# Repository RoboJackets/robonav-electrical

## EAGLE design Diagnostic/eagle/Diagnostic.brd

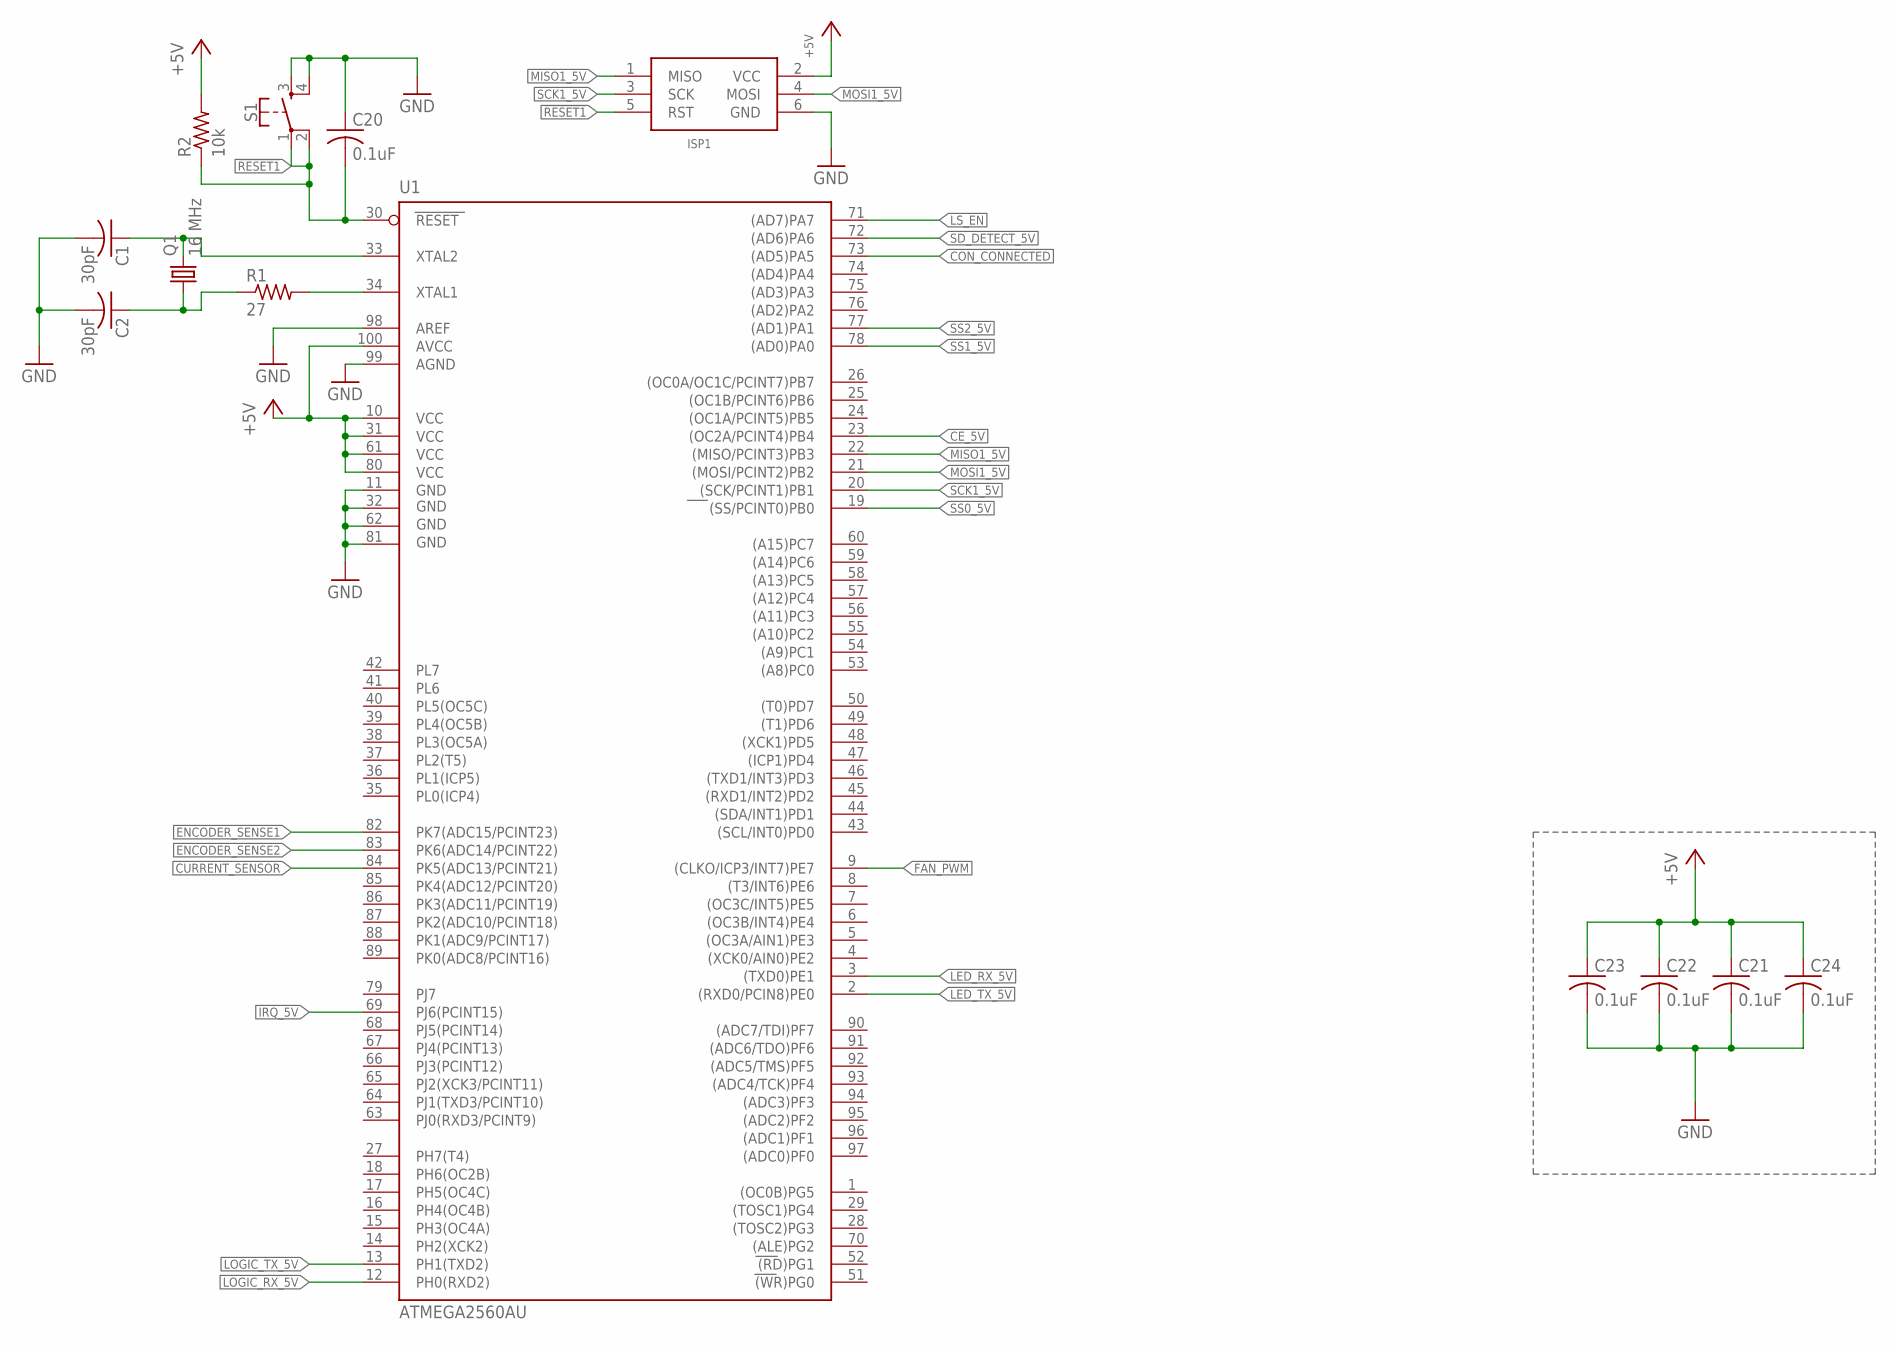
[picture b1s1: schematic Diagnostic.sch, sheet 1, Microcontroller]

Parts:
C1, C2: 30pF; C0603
C20, C21, C22, C23, C24: 0.1uF; C0603
ISP1: AVRISP-6; AVRISP
Q1: 16 MHz; HC49UP
R1: 27; R0603
R2: 10k; R0603
S1: MOMENTARY-SWITCH-SPST-2-SMD-5.2MM; TACTILE_SWITCH_SMD_5.2MM
U1: ATMEGA2560AU; TQFP100

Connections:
!RESET1: C20.2, ISP1.5 (RST), R2.1, S1.1, S1.2, U1.30 (RESET)
CE_5V: U1.23 ((OC2A/PCINT4)PB4); also elsewhere on the board
CON_CONNECTED: U1.73 ((AD5)PA5); also elsewhere on the board
CURRENT_SENSOR: U1.84 (PK5(ADC13/PCINT21)); also elsewhere on the board
ENCODER_SENSE1: U1.82 (PK7(ADC15/PCINT23)); also elsewhere on the board
ENCODER_SENSE2: U1.83 (PK6(ADC14/PCINT22)); also elsewhere on the board
FAN_PWM: U1.9 ((CLKO/ICP3/INT7)PE7); also elsewhere on the board
GND: C1.2, C2.2, C20.1, C21.2, C22.2, C23.2, C24.2, ISP1.6 (GND), S1.3, S1.4, U1.11 (GND), U1.32 (GND1), U1.62 (GND2), U1.81 (GND3), U1.98 (AREF), U1.99 (AGND); also elsewhere on the board
IRQ_5V: U1.69 (PJ6(PCINT15)); also elsewhere on the board
LED_RX_5V: U1.3 ((TXD0)PE1); also elsewhere on the board
LED_TX_5V: U1.2 ((RXD0/PCIN8)PE0); also elsewhere on the board
LOGIC_RX_5V: U1.12 (PH0(RXD2)); also elsewhere on the board
LOGIC_TX_5V: U1.13 (PH1(TXD2)); also elsewhere on the board
LS_EN: U1.71 ((AD7)PA7); also elsewhere on the board
MISO1_5V: ISP1.1 (MISO), U1.22 ((MISO/PCINT3)PB3); also elsewhere on the board
MOSI1_5V: ISP1.4 (MOSI), U1.21 ((MOSI/PCINT2)PB2); also elsewhere on the board
unnamed: C2.1, Q1.1, R1.1
unnamed: C1.1, Q1.2, U1.33 (XTAL2)
unnamed: R1.2, U1.34 (XTAL1)
SCK1_5V: ISP1.3 (SCK), U1.20 ((SCK/PCINT1)PB1); also elsewhere on the board
SD_DETECT_5V: U1.72 ((AD6)PA6); also elsewhere on the board
SS0_5V: U1.19 ((SS/PCINT0)PB0); also elsewhere on the board
SS1_5V: U1.78 ((AD0)PA0); also elsewhere on the board
SS2_5V: U1.77 ((AD1)PA1); also elsewhere on the board

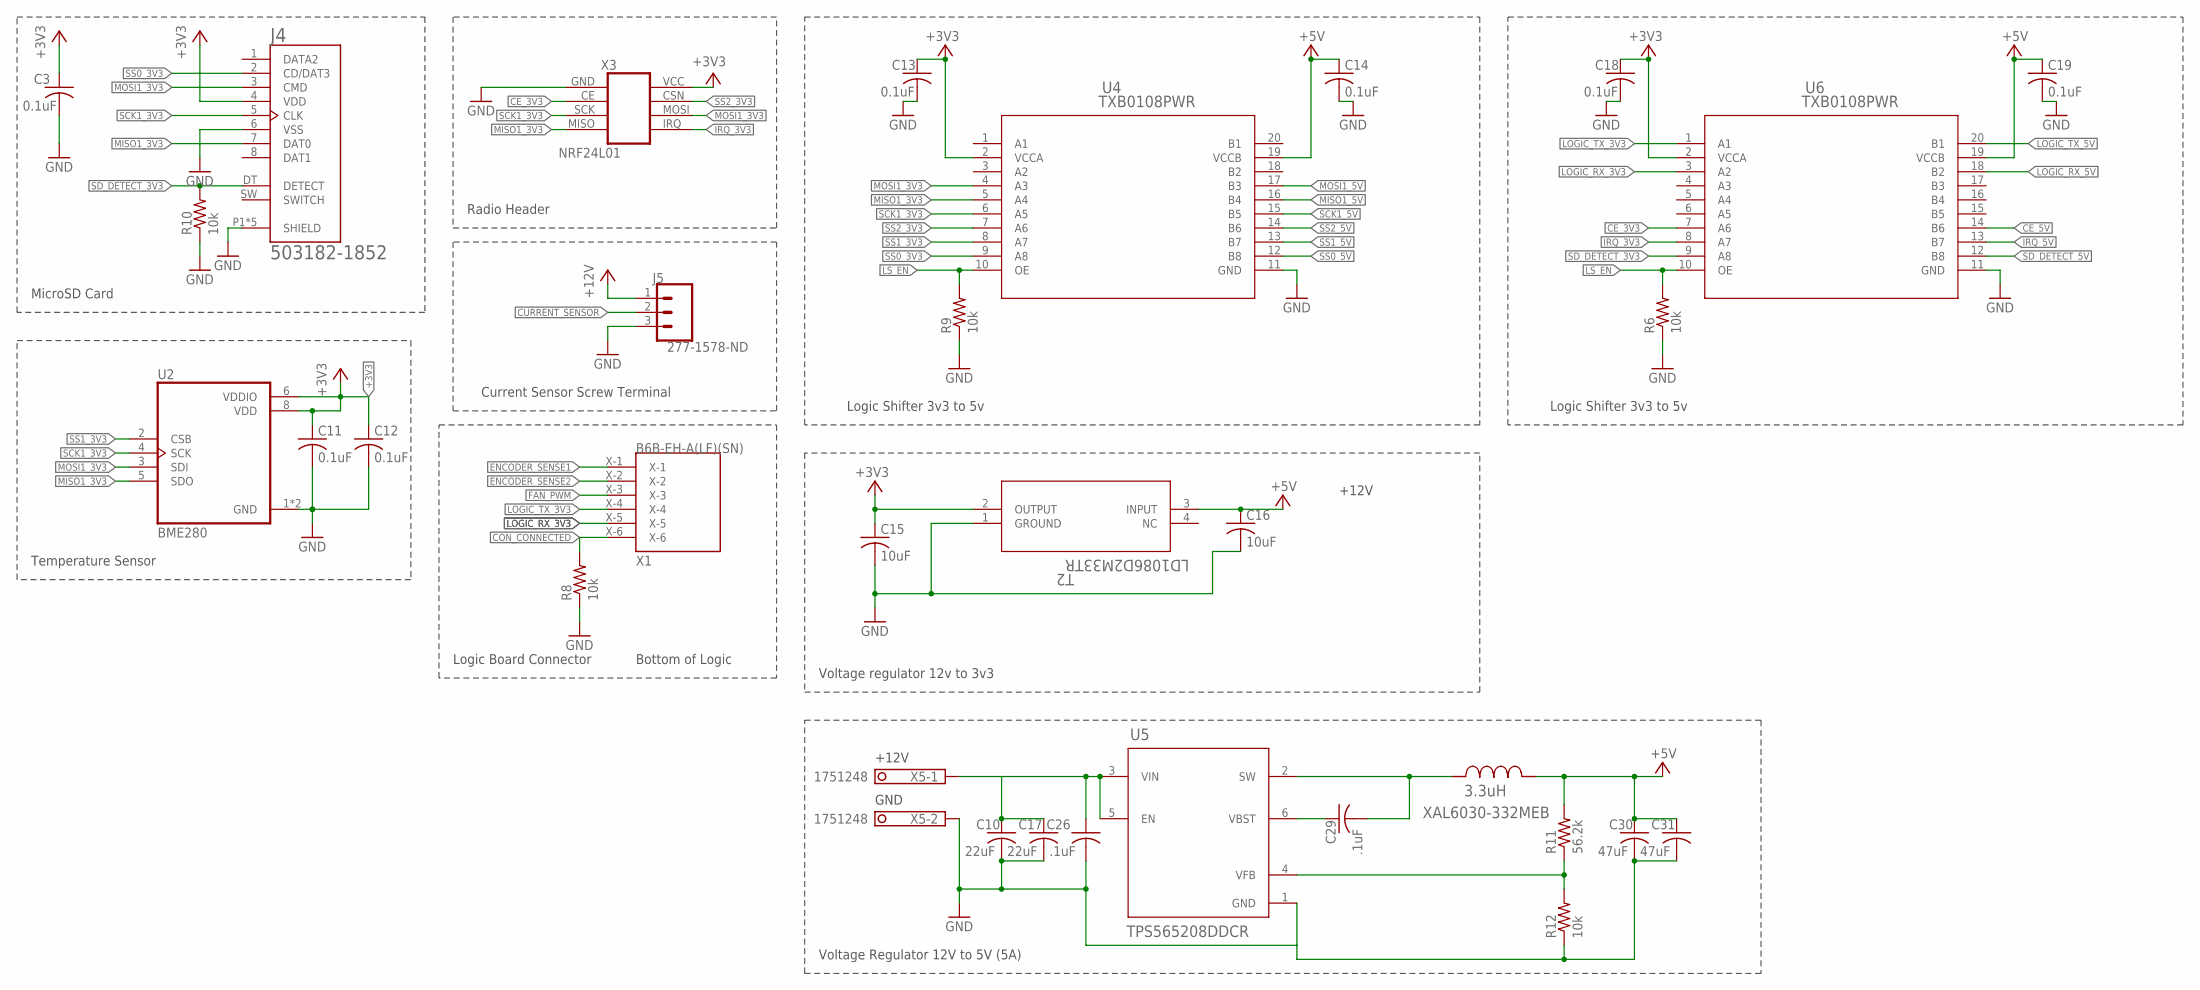
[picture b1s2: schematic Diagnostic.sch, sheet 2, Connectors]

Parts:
C3, C11, C12, C13, C14, C18, C19: 0.1uF; C0603
C10, C17: 22uF; C0603
C15, C16: 10uF; C1206
C26, C29: .1uF; C0603
C30, C31: 47uF; C0603
J4: 503182-1852; MOLEX_503182-1852
J5: 277-1578-ND; SCREWTERMINAL-5MM-3
R6, R8, R9, R10, R12: 10k; R0603
R11: 56.2k; R0603
T2: LD1086D2M33TR; D2PAK/A
U2: BME280; PSON65P250X250X100-8N
U4, U6: TXB0108PWR; PW20
U5: TPS565208DDCR; DDC0006A_N
X1: B6B-EH-A(LF)(SN); B6BEHALFSN
X3: NRF24L01; NRF24L01+PA+LNA
X5: 1751248
XAL6030-332MEB: 3.3uH; XAL6030

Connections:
+3.3V: X3.VCC
+12V: C10.1, C17.1, C26.1, J5.1, U5.3 (VIN), U5.5 (EN), X5.1
CE_3V3: U6.7 (A6), X3.CE
CE_5V: U6.14 (B6); also elsewhere on the board
CON_CONNECTED: R8.2, X1.X-6; also elsewhere on the board
CURRENT_SENSOR: J5.2; also elsewhere on the board
ENCODER_SENSE1: X1.X-1; also elsewhere on the board
ENCODER_SENSE2: X1.X-2; also elsewhere on the board
FAN_PWM: X1.X-3; also elsewhere on the board
GND: C3.2, C10.2, C11.2, C12.2, C13.2, C14.2, C15.2, C16.2, C17.2, C18.2, C19.2, C26.2, C30.2, C31.2, J4.6 (VSS), J4.P1 (SHIELD), J4.P2 (SHIELD), J4.P3 (SHIELD), J4.P4 (SHIELD), J4.P5 (SHIELD), J5.3, R6.1, R8.1, R9.1, R10.1, R12.1, T2.1 (GROUND), U2.1 (GND), U2.7 (GND), U4.11 (GND), U5.1 (GND), U6.11 (GND), X3.GND, X5.2; also elsewhere on the board
IRQ_3V3: U6.8 (A7), X3.IRQ
IRQ_5V: U6.13 (B7); also elsewhere on the board
LOGIC_RX_3V3: U6.3 (A2), X1.X-5
LOGIC_RX_5V: U6.18 (B2); also elsewhere on the board
LOGIC_TX_3V3: U6.1 (A1), X1.X-4
LOGIC_TX_5V: U6.20 (B1); also elsewhere on the board
LS_EN: R6.2, R9.2, U4.10 (OE), U6.10 (OE); also elsewhere on the board
MISO1_3V3: J4.7 (DAT0), U2.5 (SDO), U4.5 (A4), X3.MISO
MISO1_5V: U4.16 (B4); also elsewhere on the board
MOSI1_3V3: J4.3 (CMD), U2.3 (SDI), U4.4 (A3), X3.MOSI
MOSI1_5V: U4.17 (B3); also elsewhere on the board
unnamed: C29.2, U5.2 (SW), XAL6030-332MEB.1
unnamed: C29.1, U5.6 (VBST)
unnamed: R11.1, R12.2, U5.4 (VFB)
SCK1_3V3: J4.5 (CLK), U2.4 (SCK), U4.6 (A5), X3.SCK
SCK1_5V: U4.15 (B5); also elsewhere on the board
SD_DETECT_3V3: J4.DT (DETECT), R10.2, U6.9 (A8)
SD_DETECT_5V: U6.12 (B8); also elsewhere on the board
SS0_3V3: J4.2 (CD/DAT3), U4.9 (A8)
SS0_5V: U4.12 (B8); also elsewhere on the board
SS1_3V3: U2.2 (CSB), U4.8 (A7)
SS1_5V: U4.13 (B7); also elsewhere on the board
SS2_3V3: U4.7 (A6), X3.CSN
SS2_5V: U4.14 (B6); also elsewhere on the board

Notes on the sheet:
Logic Shifter 3v3 to 5v
MicroSD Card
Temperature Sensor
Current Sensor Screw Terminal
Radio Header
Voltage regulator 12v to 3v3
Voltage Regulator 12V to 5V (5A)
Logic Board Connector
+12V
GND
Bottom of Logic

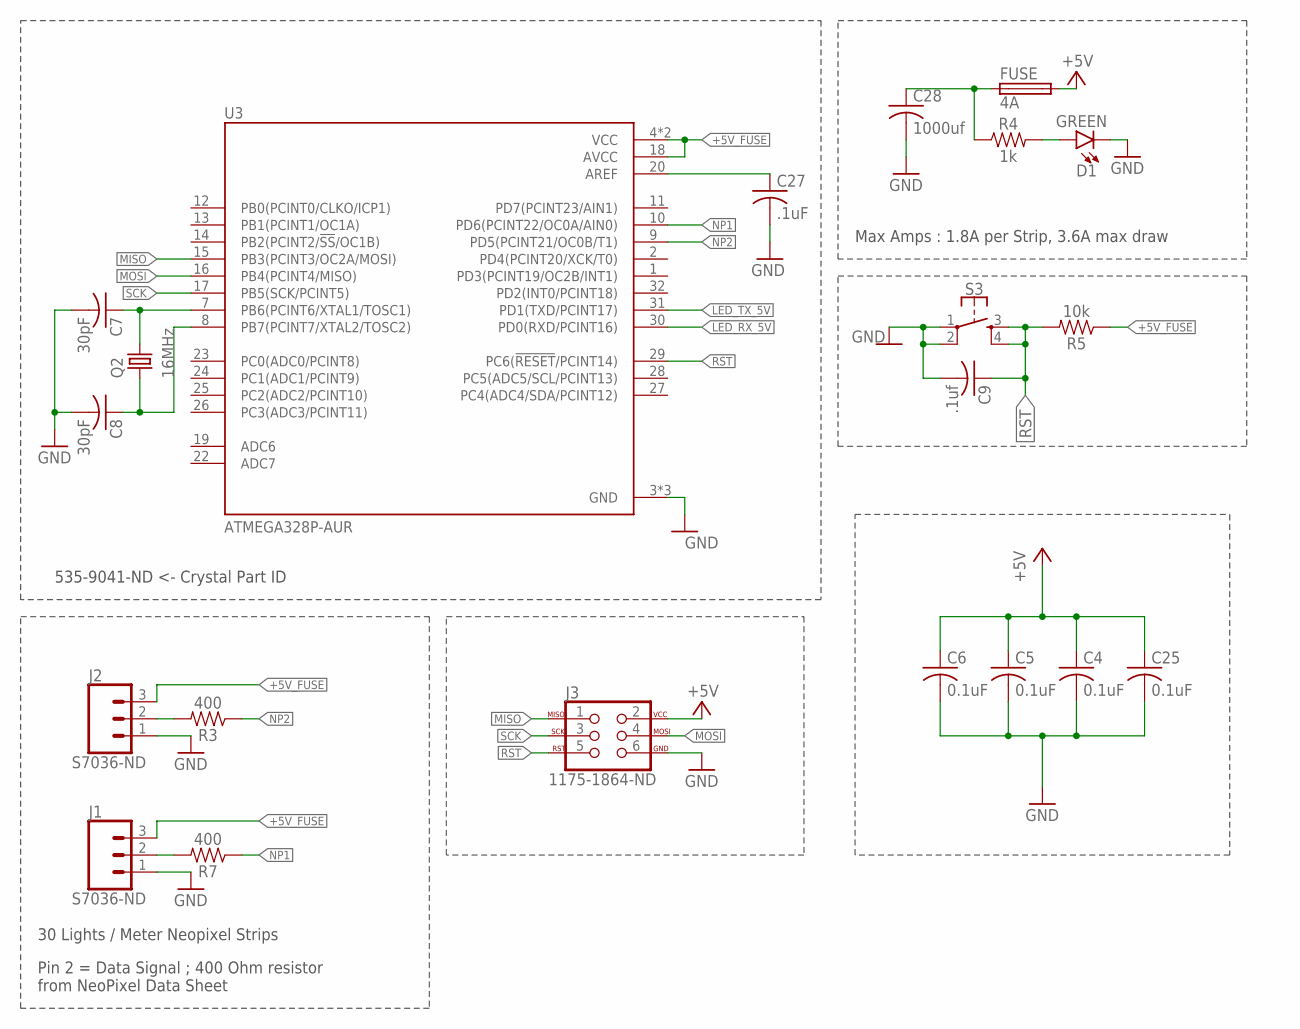
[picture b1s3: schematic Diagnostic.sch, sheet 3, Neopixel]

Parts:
C4, C5, C6, C25: 0.1uF; C0603
C7, C8: 30pF; C0603
C9: .1uf; C0603
C27: .1uF; C0603
C28: 1000uf; C0603
D1: GREEN; LED-0603
FUSE: 4A; FUSE_HOLDER
J1, J2: S7036-ND; 1X03
J3: 1175-1864-ND; 2X3-NS
Q2: 16MHz; HC49/S
R3, R7: 400; 0603
R4: 1k; 0603
R5: 10k; 0603
S3: MOMENTARY-SWITCH-SPST-2-SMD-5.2MM; TACTILE_SWITCH_SMD_5.2MM
U3: ATMEGA328P-AUR; QFP32P80_900X900X120L60X37N

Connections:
+5V_FUSE: C28.1, FUSE.P$1 (1), FUSE.P$2 (1), J1.3, J2.3, R4.1, R5.1, U3.4 (VCC), U3.6 (VCC), U3.18 (AVCC)
DATA3: J2.2, R3.2
DATA4: J1.2, R7.2
GND: C4.2, C5.2, C6.2, C7.2, C8.2, C9.2, C25.2, C27.2, C28.2, D1.C, J1.1, J2.1, J3.6, S3.1, S3.2, U3.3 (GND), U3.5 (GND), U3.21 (GND); also elsewhere on the board
LED_RX_5V: U3.30 (PD0(RXD/PCINT16)); also elsewhere on the board
LED_TX_5V: U3.31 (PD1(TXD/PCINT17)); also elsewhere on the board
MISO: J3.1, U3.15 (PB3(PCINT3/OC2A/MOSI))
MOSI: J3.4, U3.16 (PB4(PCINT4/MISO))
unnamed: D1.A, R4.2
unnamed: C27.1, U3.20 (AREF)
NP1: R7.1, U3.10 (PD6(PCINT22/OC0A/AIN0))
NP2: R3.1, U3.9 (PD5(PCINT21/OC0B/T1))
RST: C9.1, J3.5, R5.2, S3.3, S3.4, U3.29 (PC6(!RESET!/PCINT14))
SCK: J3.3, U3.17 (PB5(SCK/PCINT5))
XTAL3: C7.1, Q2.2, U3.7 (PB6(PCINT6/XTAL1/TOSC1))
XTAL4: C8.1, Q2.1, U3.8 (PB7(PCINT7/XTAL2/TOSC2))

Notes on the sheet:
Max Amps : 1.8A per Strip, 3.6A max draw
30 Lights / Meter Neopixel Strips
Pin 2 = Data Signal ; 400 Ohm resistor from NeoPixel Data Sheet
535-9041-ND <- Crystal Part ID

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
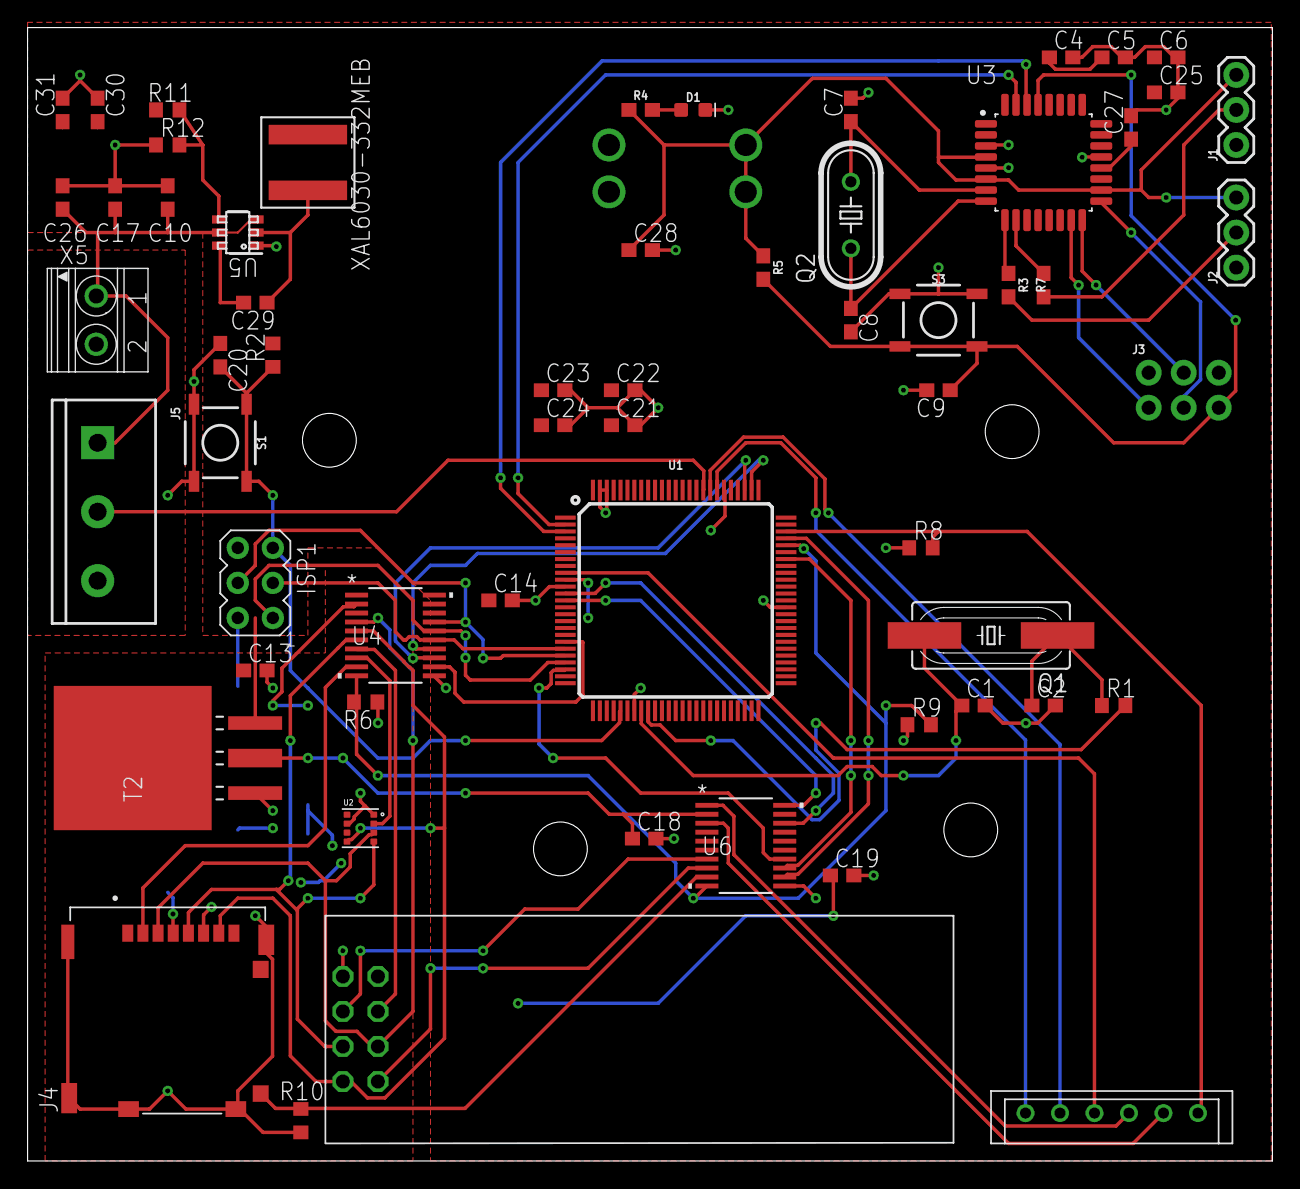
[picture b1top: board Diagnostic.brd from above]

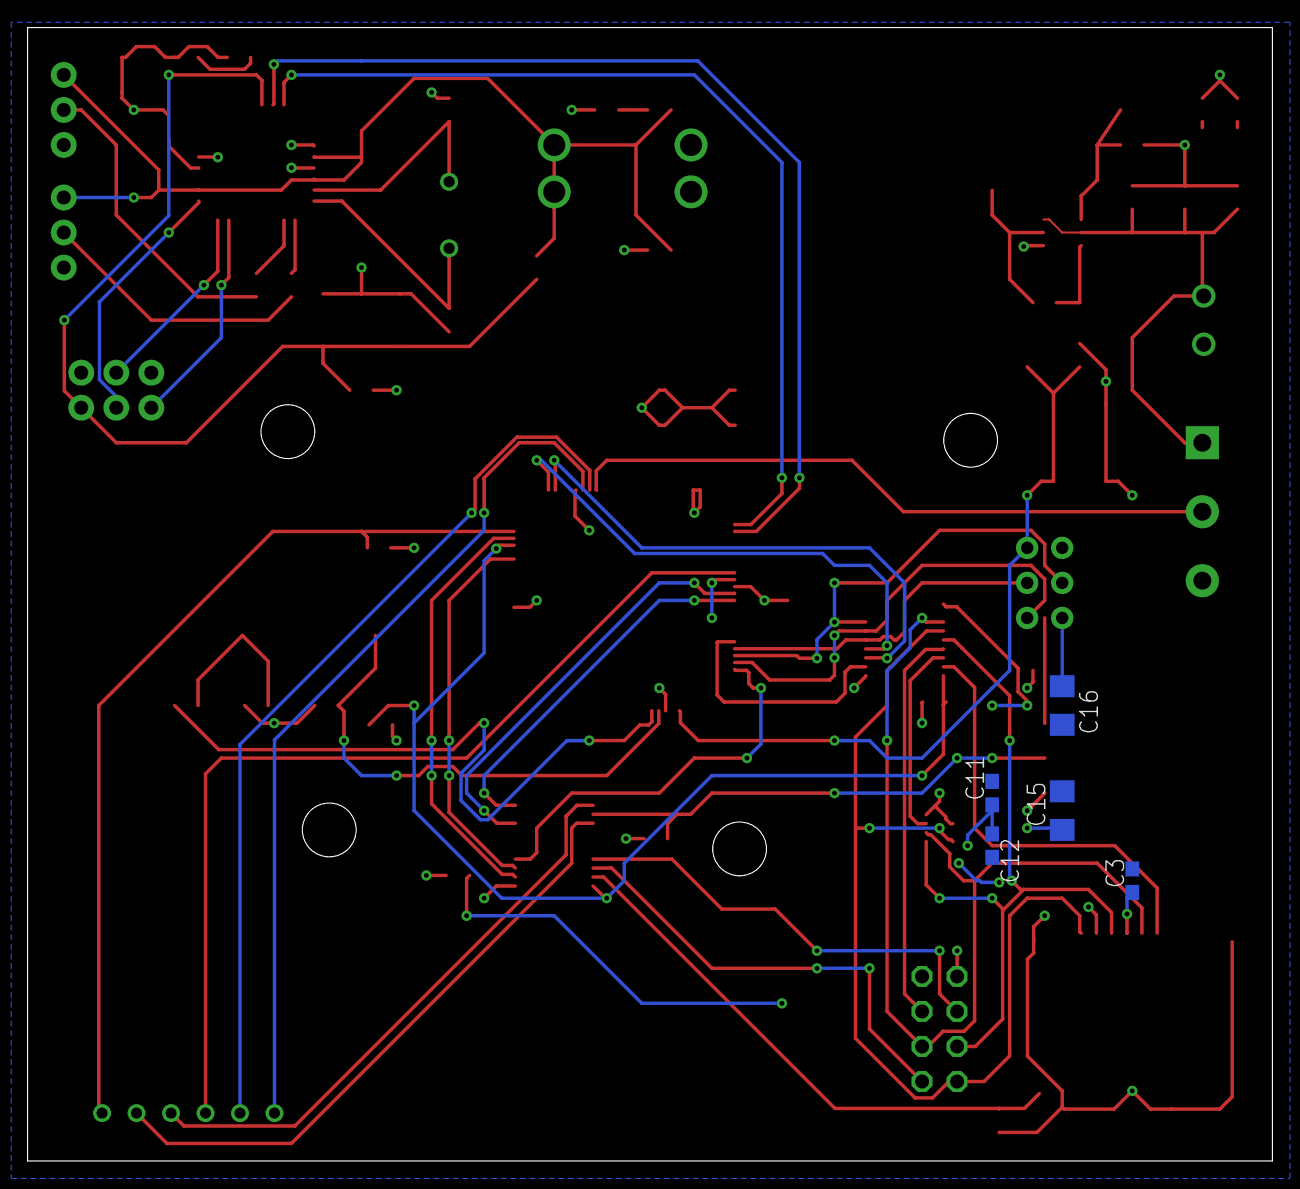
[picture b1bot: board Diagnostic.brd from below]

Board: 2 copper layers, 90.2 x 82.2 mm, 70 parts (5 on the bottom side), 54 nets.

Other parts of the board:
U$1, U$2, U$3, U$4: STANDOFF-HOLE

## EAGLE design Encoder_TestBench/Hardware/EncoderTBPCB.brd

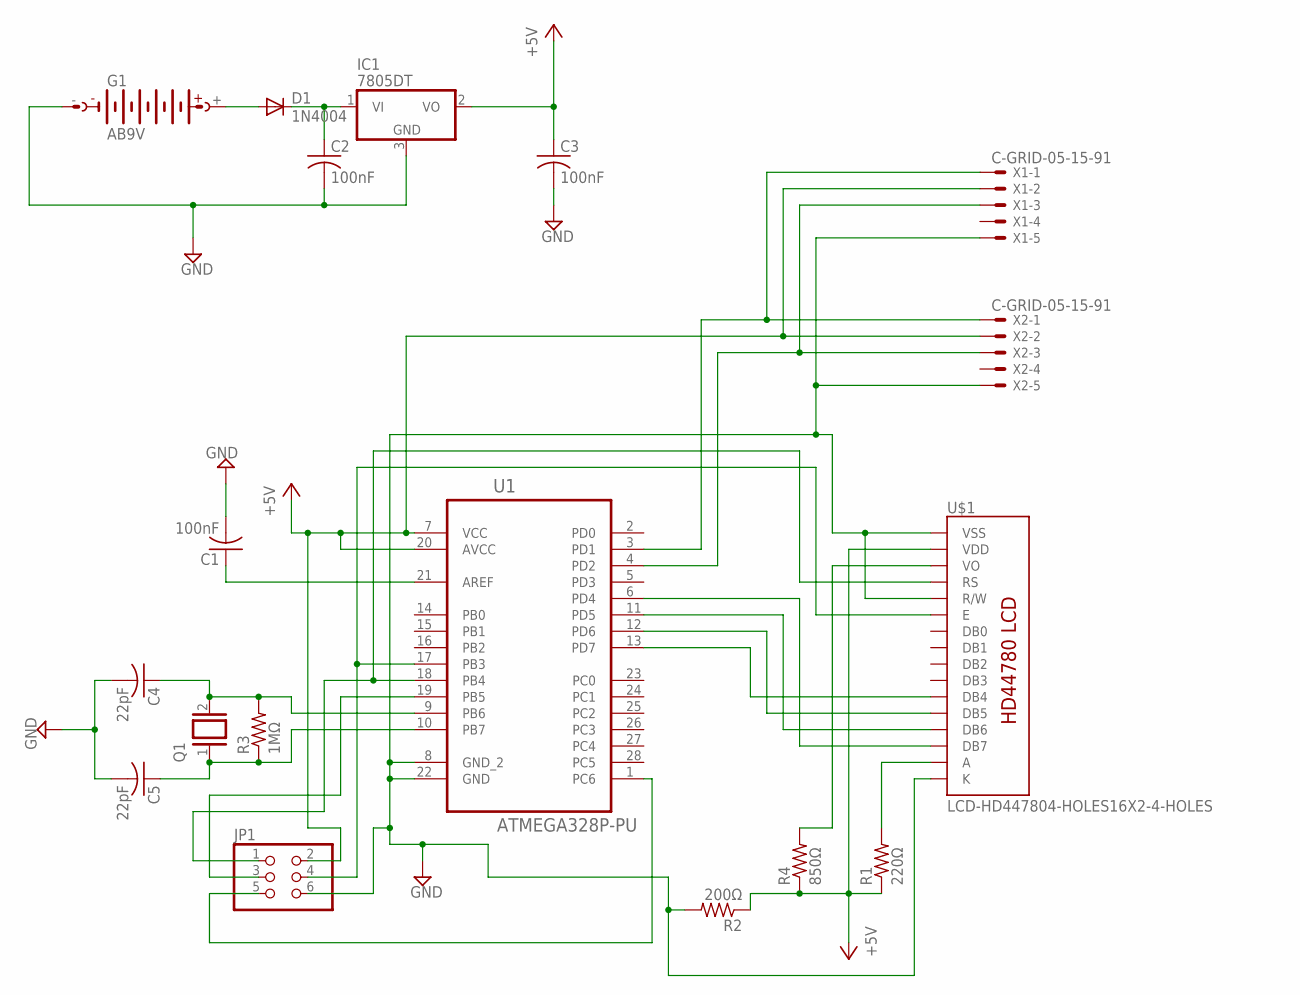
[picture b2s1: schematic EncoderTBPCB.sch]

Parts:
C1, C2, C3: 100nF; C0603
C4, C5: 22pF; C0603
D1: 1N4004; DO41-10
G1: AB9V
IC1: 7805DT; TO252
JP1: PINHD-2X3; 2X03
Q1: XTAL/S; QS
R1: 220Ω; R0603
R2: 200Ω; R0603
R3: 1MΩ; R0603
R4: 850Ω; R0603
U1: ATMEGA328P-PU; DIP254P762X457-28
U$1: LCD-HD447804-HOLES16X2-4-HOLES; LCD-16X2-4HOLES
X1, X2: C-GRID-05-15-91; 15-91-05

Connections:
unnamed: JP1.4, U1.17 (PB3), U$1.6 (E)
unnamed: R1.2, U$1.15 (A)
unnamed: U1.6 (PD4), U$1.14 (DB7)
unnamed: U1.11 (PD5), U$1.13 (DB6)
unnamed: U1.12 (PD6), U$1.12 (DB5)
unnamed: U1.13 (PD7), U$1.11 (DB4)
unnamed: JP1.1, U1.18 (PB4), U$1.4 (RS)
unnamed: C4.1, Q1.2, R3.2, U1.9 (PB6)
unnamed: C5.1, Q1.1, R3.1, U1.10 (PB7)
unnamed: C1.1, U1.21 (AREF)
unnamed: U1.3 (PD1), X1.1, X2.1
unnamed: U1.4 (PD2), X1.3, X2.3
unnamed: D1.A, G1.+
unnamed: C2.1, D1.C, IC1.1 (VI)
unnamed: JP1.3, U1.19 (PB5)
unnamed: JP1.5, U1.1 (PC6)
VDD: C3.1, IC1.2 (VO), JP1.2, R1.1, R2.1, R4.1, U1.7 (VCC), U1.20 (AVCC), U$1.2 (VDD), X1.2, X2.2
VO: R4.2, U$1.3 (VO)
VSS: C1.2, C2.2, C3.2, C4.2, C5.2, G1.-, IC1.3 (GND), JP1.6, R2.2, U1.8 (GND_2), U1.22 (GND), U$1.1 (VSS), U$1.5 (R/W), U$1.16 (K), X1.5, X2.5

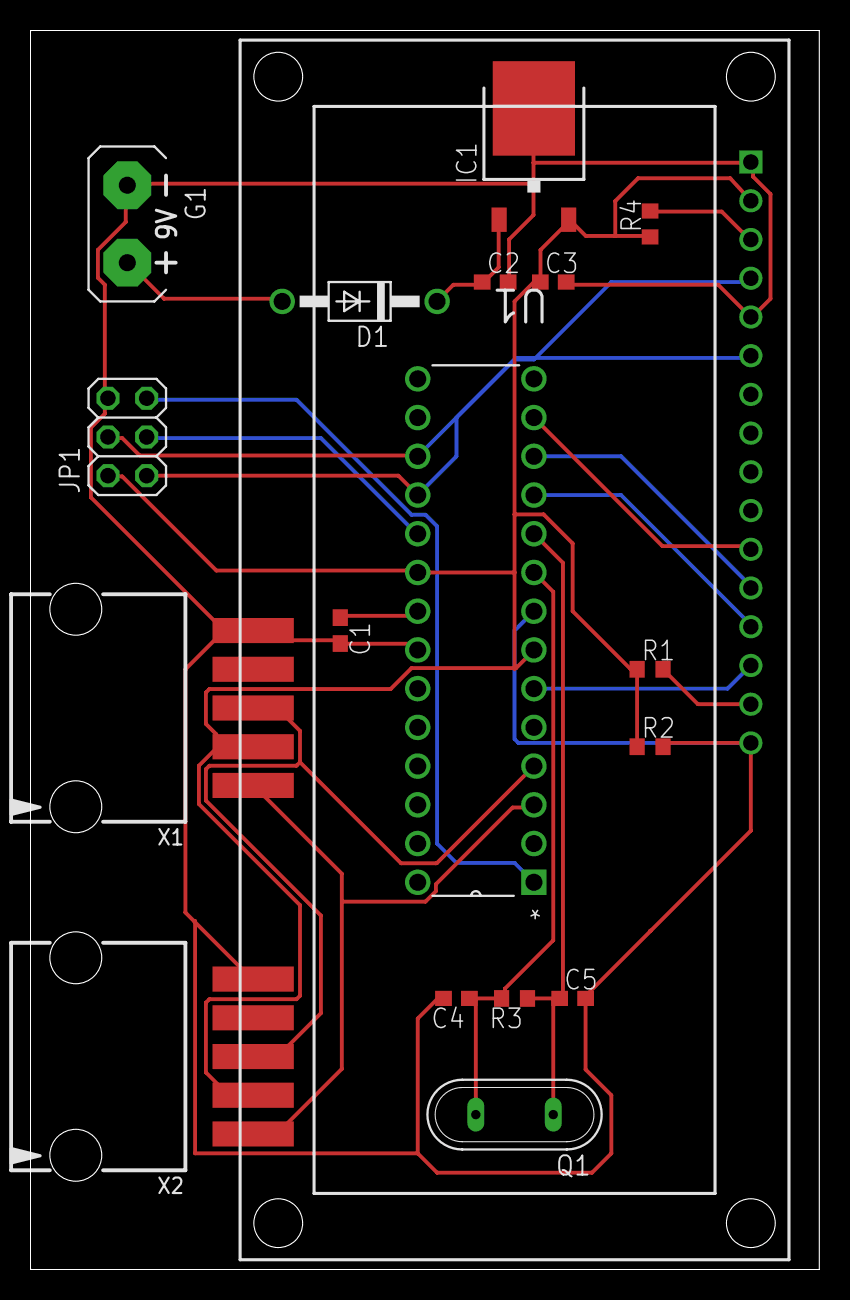
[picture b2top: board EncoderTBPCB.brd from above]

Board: 2 copper layers, 51.7 x 81.3 mm, 18 parts (0 on the bottom side), 19 nets.

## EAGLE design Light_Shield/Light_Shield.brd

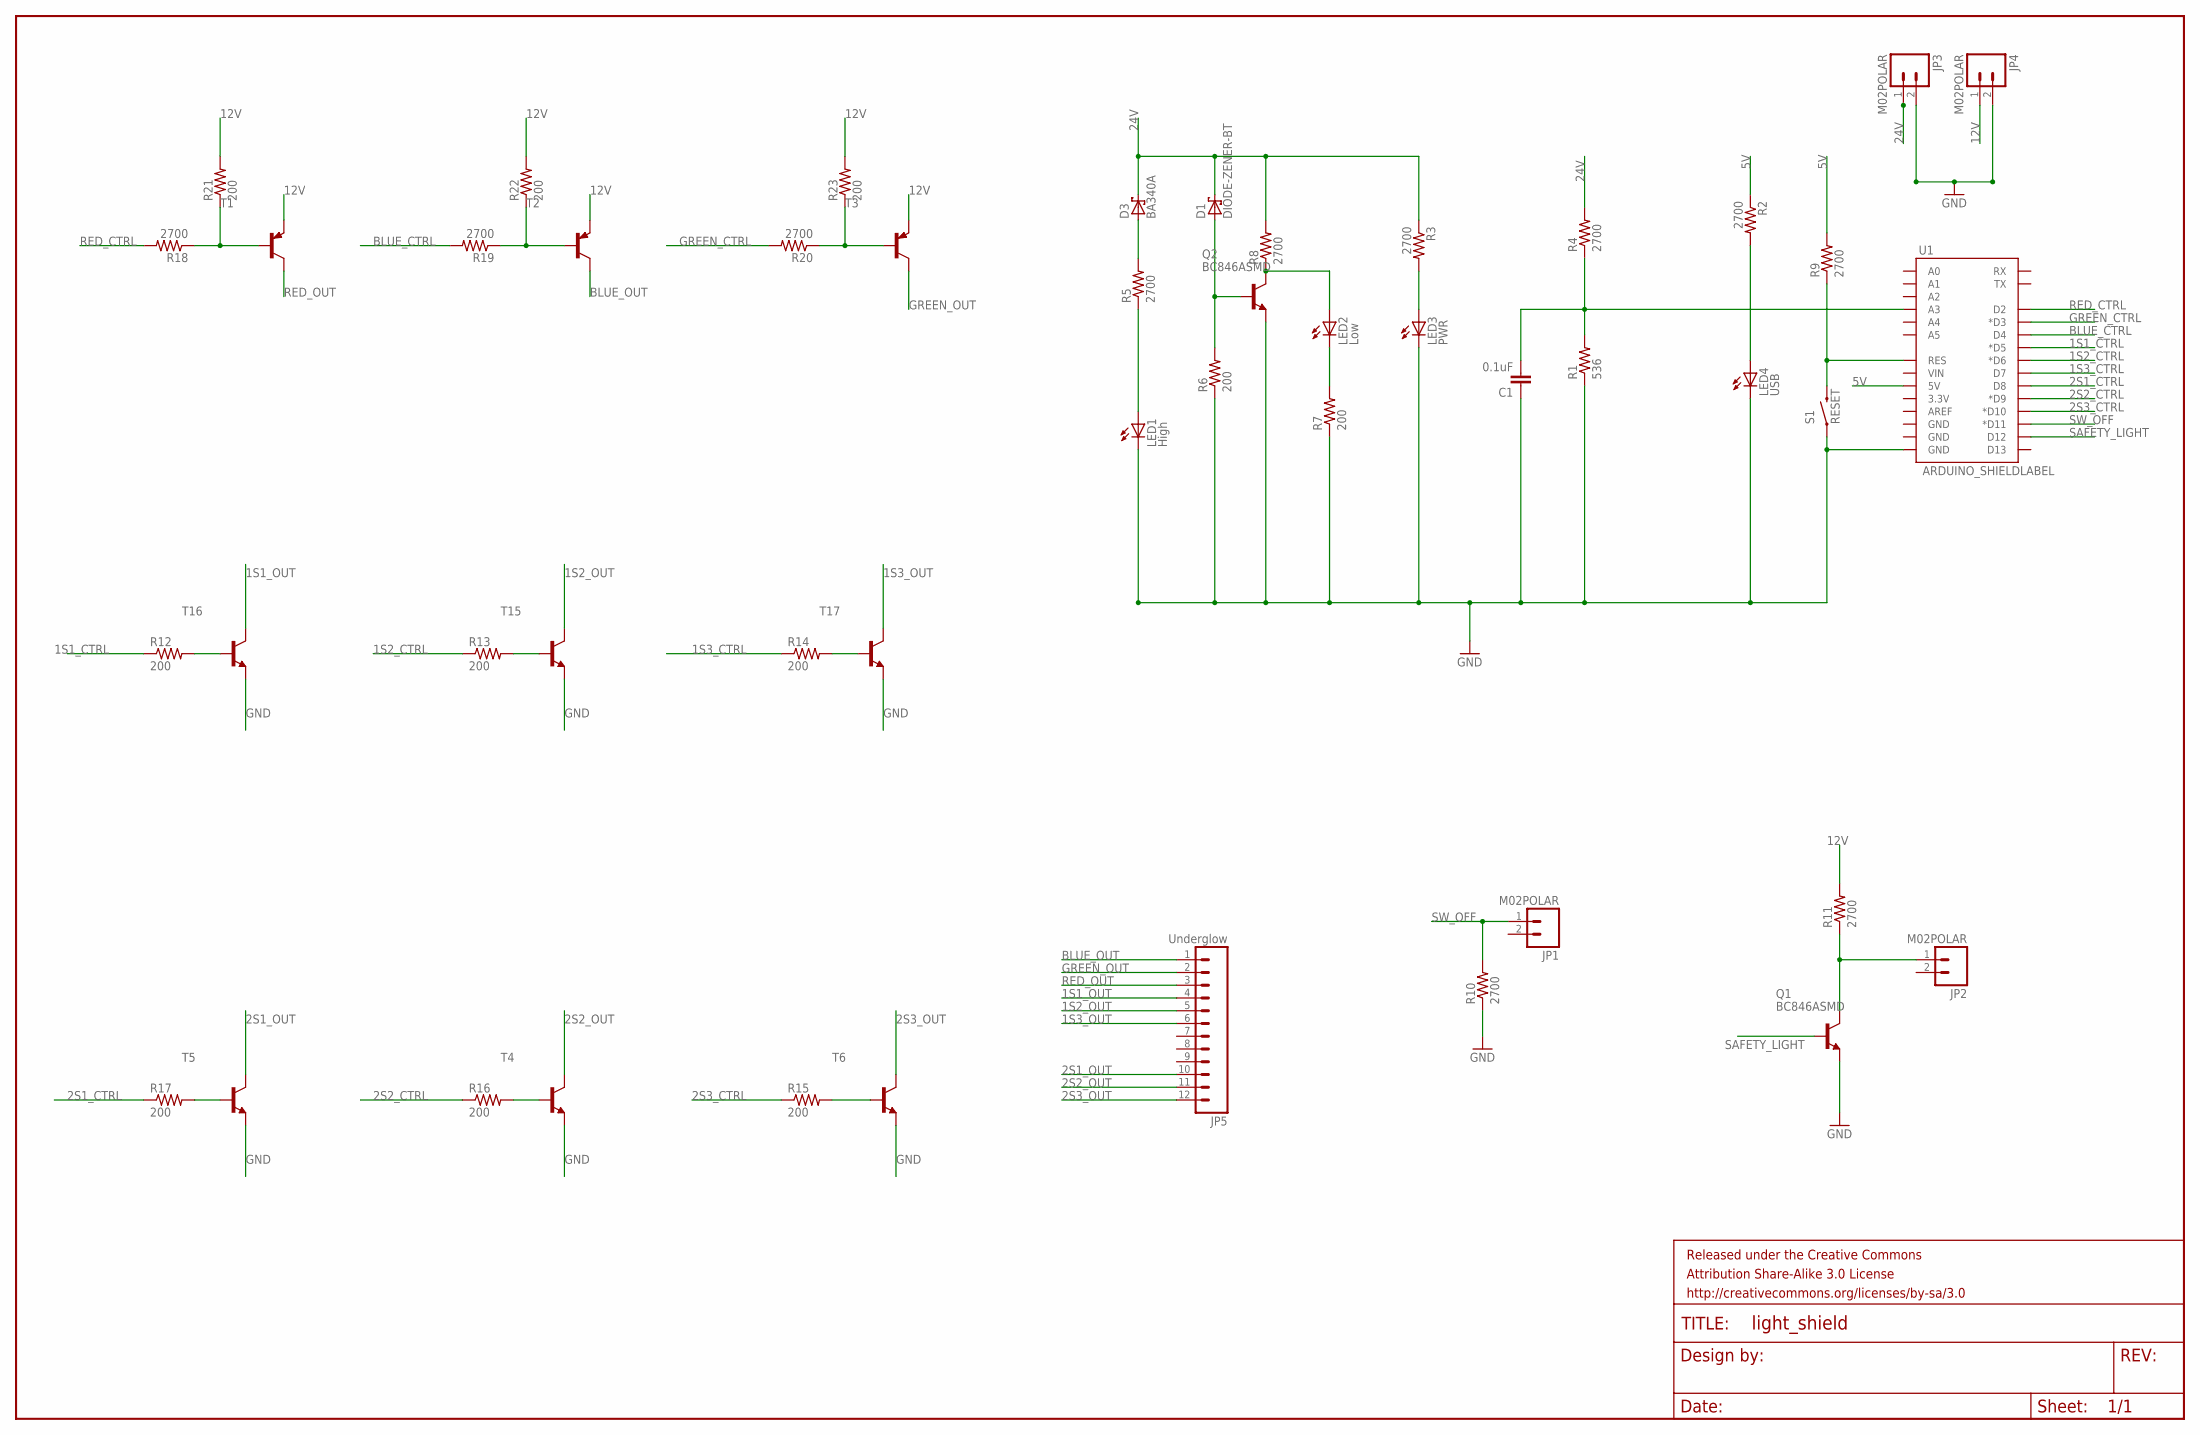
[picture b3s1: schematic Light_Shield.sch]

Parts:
C1: 0.1uF; 0402-CAP
D1: DIODE-ZENER-BT; SOD123FL
D3: BA340A; SOD123FL
FRAME1: FRAME-LEDGER; CREATIVE_COMMONS
JP1, JP2, JP3, JP4: M02POLAR; MOLEX-1X2
JP5: Underglow; 1X12_LOCK_LONGPADS
LED1: High; SML0603
LED2: Low; SML0603
LED3: PWR; SML0603
LED4: USB; SML0603
Q1, Q2: BC846ASMD; SOT23
R1: 536; 0402-RES
R2, R3, R4, R5, R8, R9, R10, R11, R18, R19, R20: 2700; 0603-RES
R6, R7, R12, R13, R14, R15, R16, R17, R21, R22, R23: 200; 0603-RES
S1: RESET; TACTILE-PTH
T1, T2, T3: -PNP-TO220V; TO220V
T4, T5, T6, T15, T16, T17: -NPN-TO220V; TO220V
U1: ARDUINO_SHIELDLABEL; DUEMILANOVE_SHIELD

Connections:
1S1_CTRL: R12.1, U1.D5 (*D5)
1S1_OUT: JP5.4, T16.2 (C)
1S2_CTRL: R13.1, U1.D6 (*D6)
1S2_OUT: JP5.5, T15.2 (C)
1S3_CTRL: R14.1, U1.D7
1S3_OUT: JP5.6, T17.2 (C)
2S1_CTRL: R17.1, U1.D8
2S1_OUT: JP5.10, T5.2 (C)
2S2_CTRL: R16.1, U1.D9 (*D9)
2S2_OUT: JP5.11, T4.2 (C)
2S3_CTRL: R15.1, U1.D10 (*D10)
2S3_OUT: JP5.12, T6.2 (C)
5V: R2.1, R9.2, U1.5V
12V: JP4.1, R11.2, R21.2, R22.2, R23.2, T1.3 (E), T2.3 (E), T3.3 (E)
24V: D1.C, D3.C, JP3.1, R3.1, R4.2, R8.2
BLUE_CTRL: R19.2, U1.D4
BLUE_OUT: JP5.1, T2.2 (C)
GND: C1.1, JP3.2, JP4.2, LED1.C, LED3.C, LED4.C, Q1.2 (E), Q2.2 (E), R1.1, R6.1, R7.1, R10.1, S1.1, T4.3 (E), T5.3 (E), T6.3 (E), T15.3 (E), T16.3 (E), T17.3 (E), U1.GND@0 (GND)
GREEN_CTRL: R20.2, U1.D3 (*D3)
GREEN_OUT: JP5.2, T3.2 (C)
unnamed: C1.2, R1.2, R4.1, U1.A3
unnamed: LED3.A, R3.2
unnamed: LED2.A, Q2.3 (C), R8.1
unnamed: D1.A, Q2.1 (B), R6.2
unnamed: LED4.A, R2.2
unnamed: JP2.1, Q1.3 (C), R11.1
unnamed: D3.A, R5.2
unnamed: LED1.A, R5.1
unnamed: R18.1, R21.1, T1.1 (B)
unnamed: LED2.C, R7.2
unnamed: R17.2, T5.1 (B)
unnamed: R9.1, S1.3 (2), U1.RES
unnamed: R16.2, T4.1 (B)
unnamed: R15.2, T6.1 (B)
unnamed: R14.2, T17.1 (B)
unnamed: R13.2, T15.1 (B)
unnamed: R12.2, T16.1 (B)
unnamed: R19.1, R22.1, T2.1 (B)
unnamed: R20.1, R23.1, T3.1 (B)
RED_CTRL: R18.2, U1.D2
RED_OUT: JP5.3, T1.2 (C)
SAFETY_LIGHT: Q1.1 (B), U1.D12
SW_OFF: JP1.1, R10.2, U1.D11 (*D11)

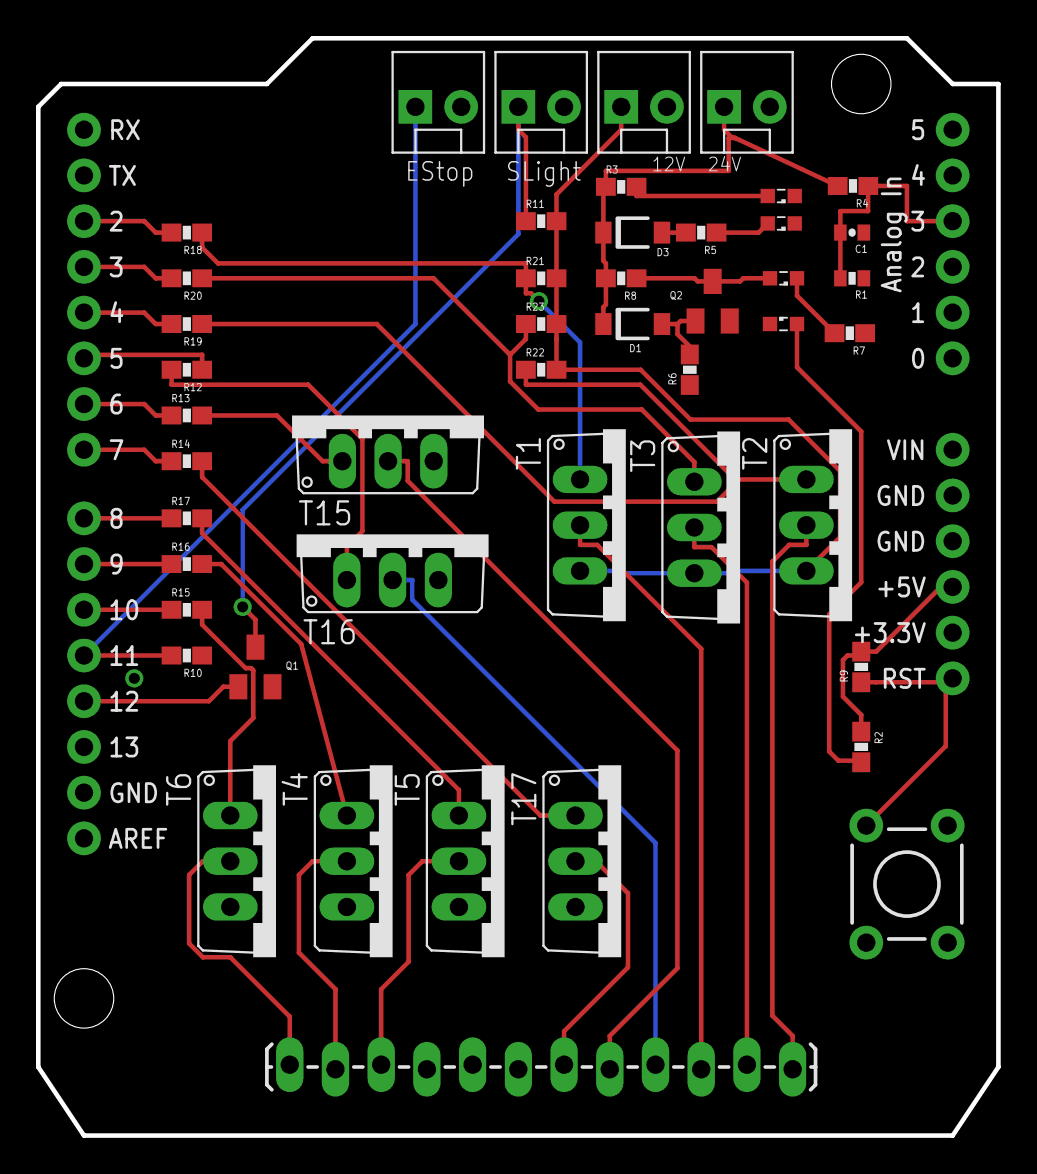
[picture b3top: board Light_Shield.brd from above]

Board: 2 copper layers, 53.3 x 61.0 mm, 49 parts (0 on the bottom side), 43 nets.

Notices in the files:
parts and their libraries:
SparkFun-LED: Licensing: Creative Commons ShareAlike 4.0 International - https://creativecommons.org/licenses/by-sa/4.0
SparkFun-Boards: Licensing: CC v3.0 Share-Alike You are welcome to use this library for commercial purposes.
SparkFun-Aesthetics: http://creativecommons.org/licenses/by-sa/3.0
